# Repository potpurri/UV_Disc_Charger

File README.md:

## Overview

This project presents a UV disc charger designed to illuminate glow-in-the-dark disc golf discs using 100 UV LEDs.

The circuit is powered by a LiPo battery, which is charged through a TP4056 with DW01A protection. The LEDs are driven by a TPS63020 buck/boost converter, and the battery is charged via a USB-C port.

**Note:** This project is a work in progress, aimed at exploring and learning more about these technologies.

## Features

The board includes the following components:

- **TP4056**: Monitors and manages the charging process.
- **DW01A Protection**: Ensures safe charging of the LiPo battery.
- **TPS63020 Buck/Boost Converter**: Efficiently drives 100 UV LEDs.
- **USB-C Port**: Enables battery charging.
- **Adjustable Charging Current**: The charging current is set using resistor R9, with the following settings:

| Resistor (Ω) | Charging Current (mA) |
|--------------|------------------------|
| 10k          | 130                    |
| 4k7          | 280                    |
| 3k           | 400                    |
| 2k           | 580                    |
| 1k5          | 780                    |
| 1k2          | 1000                   |

Image showing the battery being charged at approximately 500mA:

## Images

Below are renderings of the PCB:

3D render of the front view of the PCB

3D render of the back view of the PCB

Front view of the actual PCB

Back view of the actual PCB

## Real PCB Images

Below are images of the actual PCB:

Front view of the real PCB

Back view of the real PCB

## Full Assembly

**WORK IN PROGRESS**

## Schematics

For detailed schematics, please refer to the [schematic PDF](imgs/schematic.pdf).

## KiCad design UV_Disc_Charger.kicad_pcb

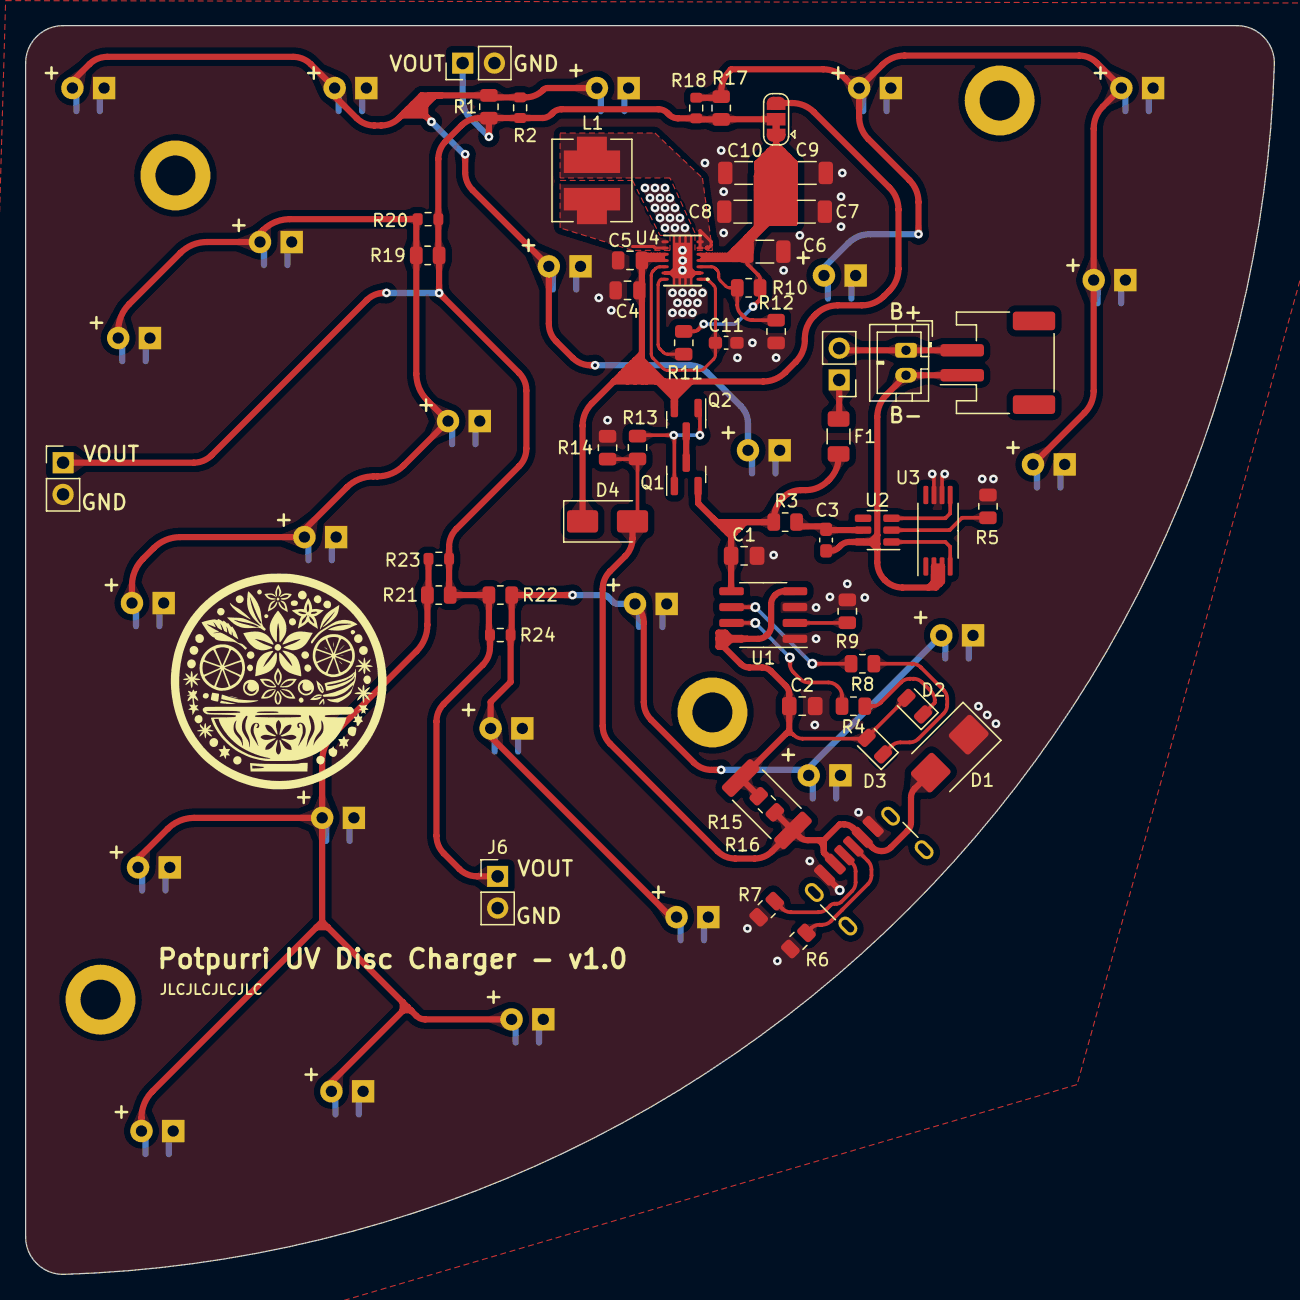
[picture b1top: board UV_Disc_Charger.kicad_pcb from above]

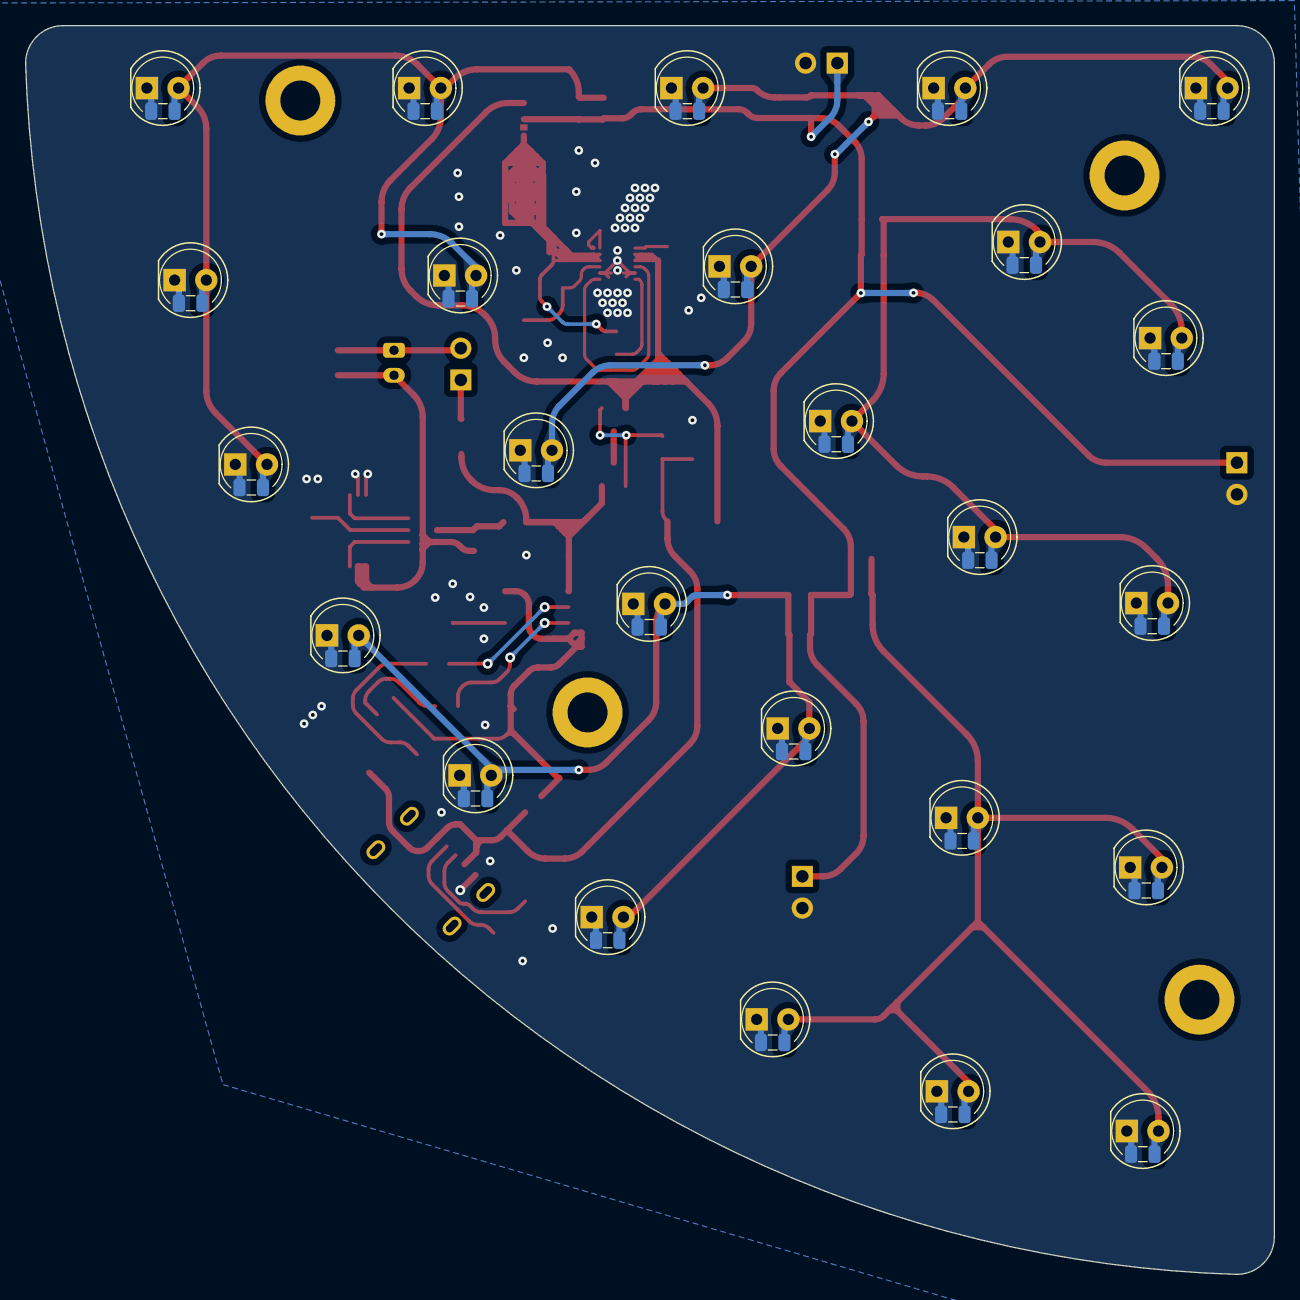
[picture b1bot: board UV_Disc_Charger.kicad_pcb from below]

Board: 2 copper layers, 100.0 x 100.0 mm, 84 parts (25 on the bottom side), 33 nets.

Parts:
C1, C2: 10u; C_0805_2012Metric_Pad1.18x1.45mm_HandSolder
C3, C11: 100n; C_0603_1608Metric_Pad1.08x0.95mm_HandSolder
C4, C5: 10u; C_0805_2012Metric
C6, C7, C8, C9: 22u; C_1206_3216Metric
C10: 100u; C_1206_3216Metric
D1: SMBJ12CA; D_SMB
D2: RED; D_0805_2012Metric
D3: GREEN; D_0805_2012Metric
D4: SS34; D_SMA
D5, D6, D7, D8, D9, D10, D11, D12, D13, D14, D15, D16, D17, D18, D19, D20, D21, D22, D23, D24, D25, D26, D27, D28, D29: LED; LED-ThroughHole-And-SMD0805
F1: 1.5A; Fuse_1206_3216Metric
H1, H2, H3, H4: MountingHole; MountingHole_3.2mm_M3_DIN965_Pad
J1: Type-C_6P; USB-C 6 Pin - Long pads
J2: JST PH Connector; JST_PH_B2B-PH-K_1x02_P2.00mm_Vertical
J3, J5, J6: Connector; PinHeader_1x02_P2.54mm_Vertical
J4: JST PH Connector; JST_PH_S2B-PH-SM4-TB_1x02-1MP_P2.00mm_Horizontal
JP1: SolderJumper_3_Bridged12; SolderJumper-3_P1.3mm_Bridged12_RoundedPad1.0x1.5mm
L1: 2u2; Combined CD43 + L 6.3x6.3
Q1, Q2: SI2301; SOT-23
R1, R17, R19, R21, R22: 0805; R_0805_2012Metric
R2, R18, R20, R23, R24: 0603; R_0603_1608Metric
R3: 100R; R_0805_2012Metric
R4, R5, R8, R13: 1k; R_0805_2012Metric
R6, R7: 5k1; R_0805_2012Metric
R9: 2k; R_0805_2012Metric
R10: 1M6; R_0805_2012Metric
R11: 1M; R_0805_2012Metric
R12: 180k; R_0805_2012Metric
R14: 10k; R_0805_2012Metric
R15: 0R4; R_0805_2012Metric
R16: 2512 package; R_2512_6332Metric
SW1: SW_SPST; PinHeader_1x02_P2.54mm_Vertical
U1: TP4056; SOP-8_3.76x4.96mm_P1.27mm
U2: DW01A; SOT-23-6
U3: FS8205A; TSSOP-8_4.4x3mm_P0.65mm
U4: TPS63020; QFN14-3X4MM

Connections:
+5V: C6.1, C7.1, C8.1, C9.1, C10.1, JP1.1 (A), R10.1, R11.1, U4.4 (VOUT), U4.5 (VOUT)
+BATT: J2.1, J4.2, SW1.2 (B)
+VSW: J3.1, J5.1, J6.1, JP1.2 (C), R1.1, R2.1, R17.1, R18.1, R19.1, R20.1, R21.1, R22.1, R23.1, R24.1
-BATT: C3.2, J2.2, J4.1, U2.6 (GND), U3.2 (S1), U3.3 (S1)
GND: C1.2, C2.2, C4.2, C5.2, C6.2, C7.2, C8.2, C9.2, C10.2, C11.2, D1.1 (A1), D5.1 (K), D6.1 (K), D7.1 (K), D8.1 (K), D9.1 (K), D10.1 (K), D11.1 (K), D12.1 (K), D13.1 (K), D14.1 (K), D15.1 (K), D16.1 (K), D17.1 (K), D18.1 (K), D19.1 (K), D20.1 (K), D21.1 (K), D22.1 (K), D23.1 (K), D24.1 (K), D25.1 (K), D26.1 (K), D27.1 (K), D28.1 (K), D29.1 (K), J1.A12 (GND), J1.B12 (GND), J3.2, J5.2, J6.2, R5.2, R6.2, R7.2, R9.2, R12.2, R14.2, U1.1 (TEMP), U1.3 (GND), U3.6 (S2), U3.7 (S2), U4.2 (GND), U4.13 (PS/SYNC), U4.15 (PGND), U4.16 (PGND), U4.17 (PGND), U4.18 (PGND), U4.19 (PGND), U4.20 (PGND), U4.21 (PGND), U4.22 (PGND), U4.23 (PGND)
unnamed: C2.1, D2.2 (A), D3.2 (A), R15.1, R16.1, U1.4 (VCC), U1.8 (CE)
unnamed: D2.1 (K), R4.1
unnamed: D3.1 (K), R8.1
unnamed: D5.2 (A), D6.2 (A), D7.2 (A), D8.2 (A), D9.2 (A), R1.2, R2.2
unnamed: D10.2 (A), D11.2 (A), D12.2 (A), D13.2 (A), D14.2 (A), R17.2, R18.2
unnamed: D15.2 (A), D16.2 (A), D17.2 (A), D18.2 (A), D19.2 (A), R19.2, R20.2
unnamed: D20.2 (A), D22.2 (A), D24.2 (A), D26.2 (A), D28.2 (A), R21.2, R23.2
unnamed: D21.2 (A), D23.2 (A), D25.2 (A), D27.2 (A), D29.2 (A), R22.2, R24.2
unnamed: J1.A5 (CC1), R7.1
unnamed: J1.B5 (CC2), R6.1
unnamed: L1.1, U4.8 (L1), U4.9 (L1)
unnamed: L1.2, U4.6 (L2), U4.7 (L2)
unnamed: Q1.3 (D), Q2.3 (D)
unnamed: Q1.1 (G), Q2.1 (G), R13.1
unnamed: C1.1, F1.2, Q1.2 (S), R3.2, U1.5 (BAT)
unnamed: F1.1, SW1.1 (A)
unnamed: R4.2, U1.7 (CHRG)
unnamed: R9.1, U1.2 (PROG)
unnamed: R8.2, U1.6 (STDBY)
unnamed: U2.3 (OC), U3.5 (G2)
unnamed: U2.1 (OD), U3.4 (G1)
unnamed: C3.1, R3.1, U2.5 (VCC)
unnamed: R5.1, U2.2 (VM)
unnamed: C11.1, U4.1 (VINA), U4.12 (EN)
unnamed: R10.2, R12.1, U4.3 (FB)
unnamed: R11.2, U4.14 (PG)
VBUS: D1.2 (A2), D4.2 (A), J1.A9 (VBUS), J1.B9 (VBUS), R13.2, R14.1, R15.2, R16.2
VCC: C4.1, C5.1, D4.1 (K), JP1.3 (B), Q2.2 (S), U4.10 (VIN), U4.11 (VIN)

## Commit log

2024-11-15 layout started
2025-01-10 added manufacturing files
2025-02-19 images
2025-02-19 added readme
2025-02-19 readme fix
